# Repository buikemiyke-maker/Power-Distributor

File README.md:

# power distributor 

# power distributor

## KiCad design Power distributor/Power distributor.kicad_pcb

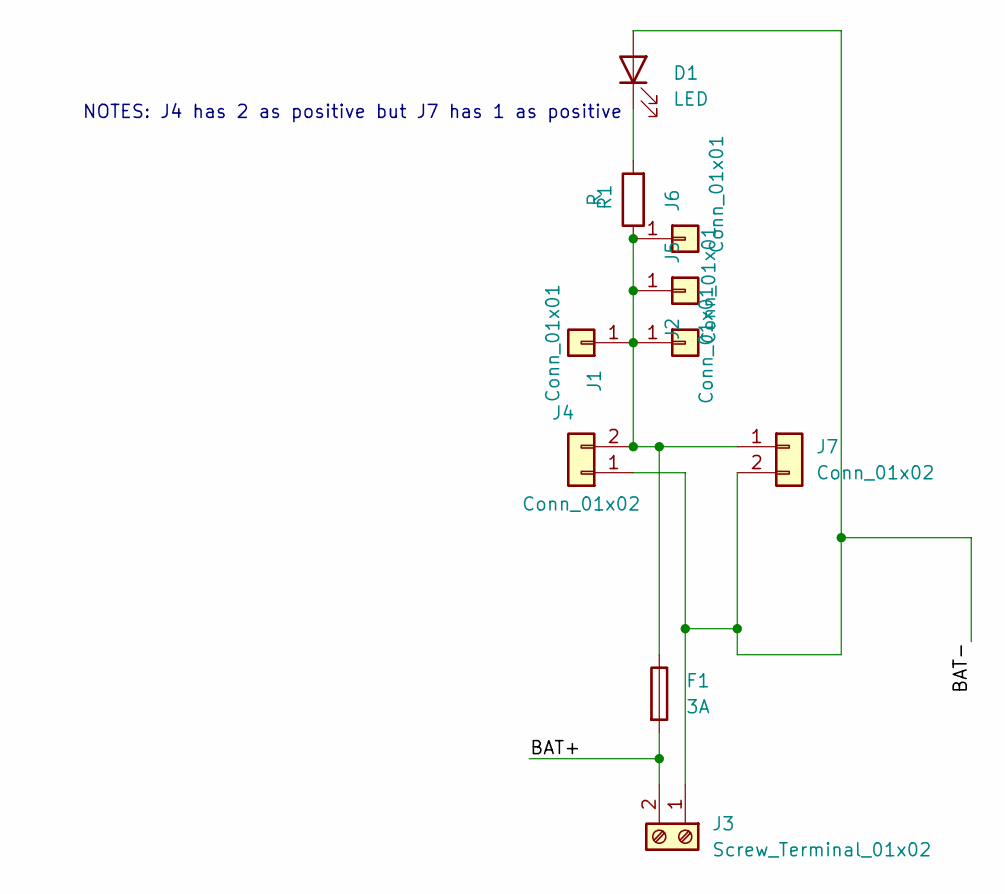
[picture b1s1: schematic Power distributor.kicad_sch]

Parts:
D1: LED; LED_D3.0mm
F1: 3A; Fuseholder_Clip-6.3x32mm_Littelfuse_102_Inline_P34.21x7.62m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
J1, J2, J5, J6: Conn_01x01; TestPoint_Pad_4.0x4.0mm
J3: Screw_Terminal_01x02; TerminalBlock_Xinya_XY308-2.54-2P_1x02_P2.54mm_Horizontal
J4, J7: Conn_01x02; AMASS_XT60-M_1x02_P7.20mm_Vertical
R1: R; R_Axial_DIN0207_L6.3mm_D2.5mm_P10.16mm_Horizontal

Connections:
/BAT+: F1.2, J3.2
/BAT-: D1.2 (A), J3.1, J4.1, J7.2
unnamed: D1.1 (K), R1.2
unnamed: F1.1, J1.1, J2.1, J4.2, J5.1, J6.1, J7.1, R1.1

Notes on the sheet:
NOTES: J4 has 2 as positive but J7 has 1 as positive

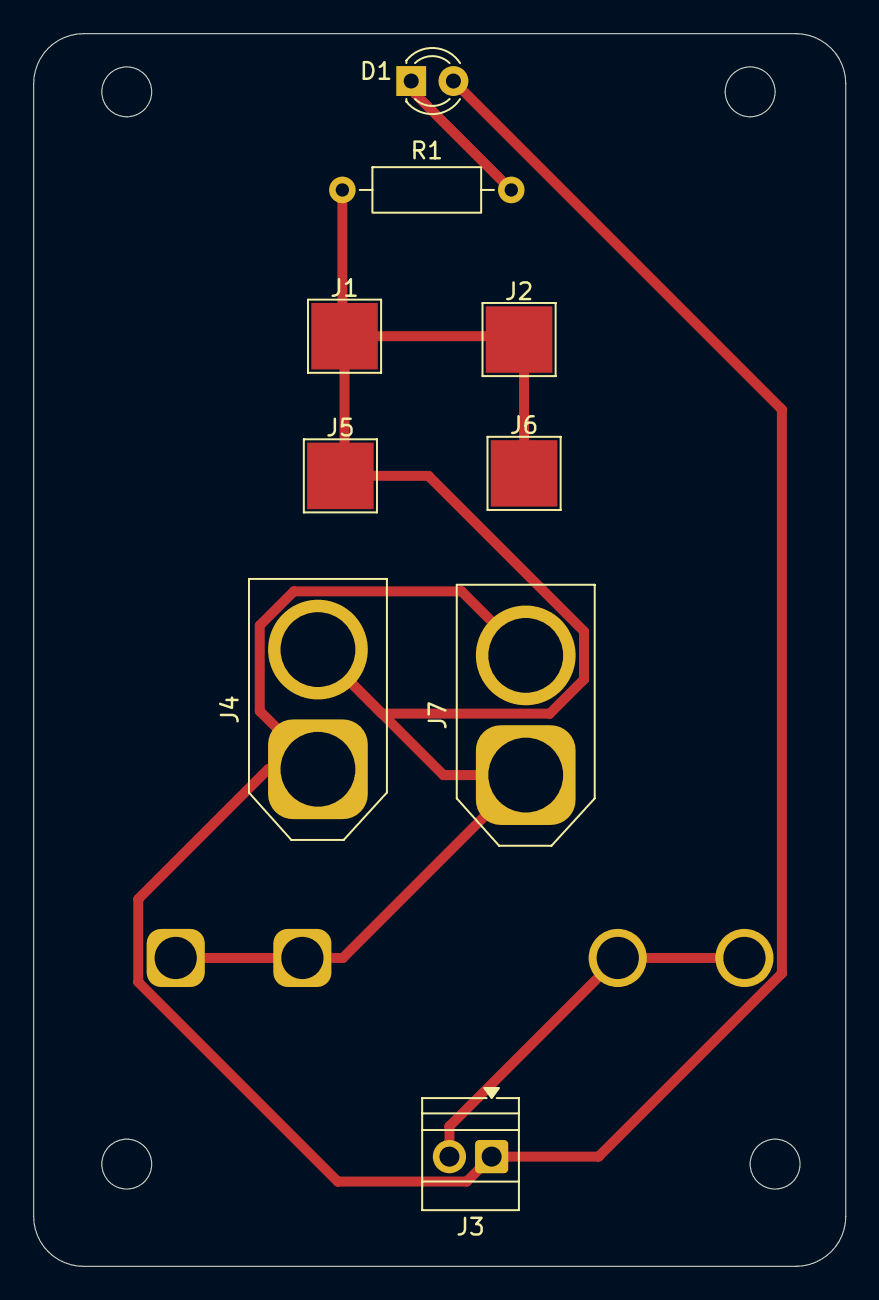
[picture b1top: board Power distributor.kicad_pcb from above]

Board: 2 copper layers, 48.8 x 74.2 mm, 10 parts (1 on the bottom side), 4 nets.

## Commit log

2026-06-22 Update project name in README
2026-06-25 Revise README title and include screenshots
    Updated project title and added images to README.
